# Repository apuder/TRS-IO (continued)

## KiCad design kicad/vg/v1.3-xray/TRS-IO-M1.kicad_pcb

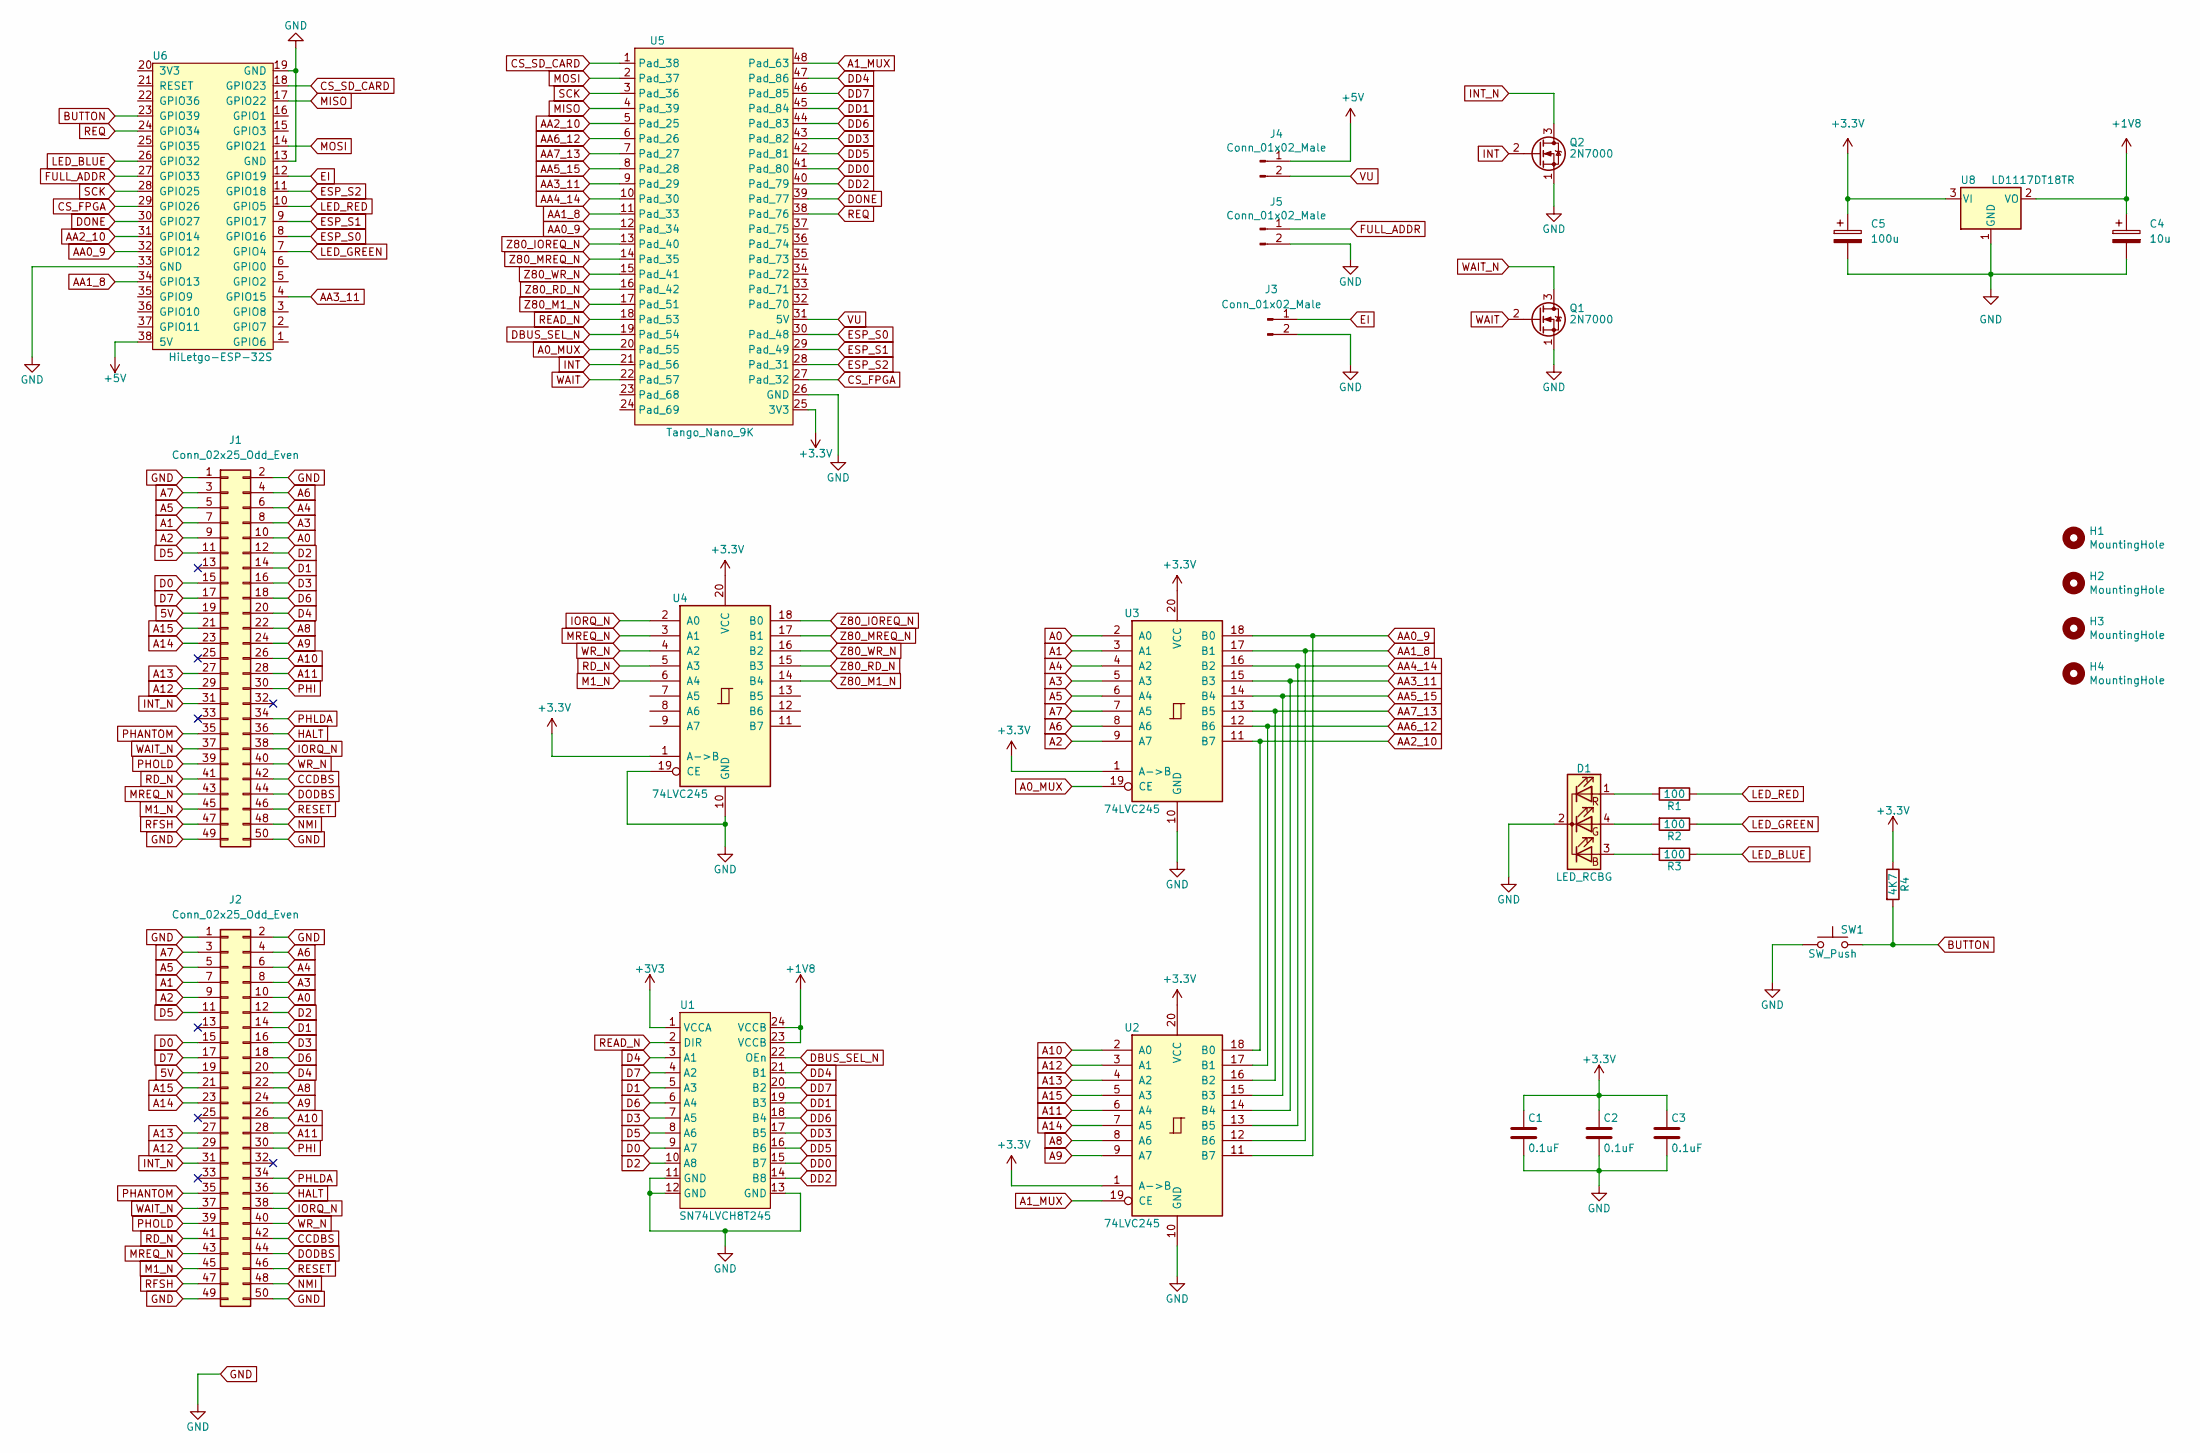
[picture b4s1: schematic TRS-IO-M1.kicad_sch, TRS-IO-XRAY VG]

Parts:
C1, C2, C3: 0.1uF; C_0805_2012Metric_Pad1.18x1.45mm_HandSolder
C4: 10u; C_1206_3216Metric_Pad1.33x1.80mm_HandSolder
C5: 100u; C_1206_3216Metric_Pad1.33x1.80mm_HandSolder
D1: LED_RCBG; LED_D5.0mm-4_RGB
H1, H2, H3, H4: MountingHole; MountingHole_3mm_Pad_Via
J1: Conn_02x25_Odd_Even; EDGE50
J2: Conn_02x25_Odd_Even; Pin_Header_Straight_2x25_Pitch2.54mm
J3, J4, J5: Conn_01x02_Male; PinHeader_1x02_P2.54mm_Vertical
Q1, Q2: 2N7000; TO-92_Inline
R1, R2, R3: 100; R_Axial_DIN0207_L6.3mm_D2.5mm_P7.62mm_Horizontal
R4: 4K7; R_Axial_DIN0207_L6.3mm_D2.5mm_P7.62mm_Horizontal
SW1: SW_Push; SW_PUSH_6mm_H9.5mm
U1: SN74LVCH8T245; TSSOP-24_4.4x7.8mm_P0.65mm
U2, U3, U4: 74LVC245; SSOP-20_5.3x7.2mm_P0.65mm
U5: Tango_Nano_9K; DIP-48_W22.9mm
U6: HiLetgo-ESP-32S; DIP-38_W22.9mm
U8: LD1117DT18TR; TO-252-3_TabPin2

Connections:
5V: J1.19, J2.19
+1V8: C4.1, U1.23 (VCCB), U1.24 (VCCB), U8.2 (VO)
+5V: J4.1, U6.38 (5V)
A0: J1.10, J2.10, U3.2 (A0)
A0_MUX: U3.19 (CE), U5.20 (Pad_55)
A1: J1.7, J2.7, U3.3 (A1)
A1_MUX: U2.19 (CE), U5.48 (Pad_63)
A2: J1.9, J2.9, U3.9 (A7)
A3: J1.8, J2.8, U3.5 (A3)
A4: J1.6, J2.6, U3.4 (A2)
A5: J1.5, J2.5, U3.6 (A4)
A6: J1.4, J2.4, U3.8 (A6)
A7: J1.3, J2.3, U3.7 (A5)
A8: J1.22, J2.22, U2.8 (A6)
A9: J1.24, J2.24, U2.9 (A7)
A10: J1.26, J2.26, U2.2 (A0)
A11: J1.28, J2.28, U2.6 (A4)
A12: J1.29, J2.29, U2.3 (A1)
A13: J1.27, J2.27, U2.4 (A2)
A14: J1.23, J2.23, U2.7 (A5)
A15: J1.21, J2.21, U2.5 (A3)
AA0_9: U2.11 (B7), U3.18 (B0), U5.12 (Pad_34), U6.32 (GPIO12)
AA1_8: U2.12 (B6), U3.17 (B1), U5.11 (Pad_33), U6.34 (GPIO13)
AA2_10: U2.18 (B0), U3.11 (B7), U5.5 (Pad_25), U6.31 (GPIO14)
AA3_11: U2.14 (B4), U3.15 (B3), U5.9 (Pad_29), U6.4 (GPIO15)
AA4_14: U2.13 (B5), U3.16 (B2), U5.10 (Pad_30)
AA5_15: U2.15 (B3), U3.14 (B4), U5.8 (Pad_28)
AA6_12: U2.17 (B1), U3.12 (B6), U5.6 (Pad_26)
AA7_13: U2.16 (B2), U3.13 (B5), U5.7 (Pad_27)
BUTTON: R4.2, SW1.2, U6.23 (GPIO39)
CCDBS: J1.42, J2.42
CS_FPGA: U5.27 (Pad_32), U6.29 (GPIO26)
CS_SD_CARD: U5.1 (Pad_38), U6.18 (GPIO23)
D0: J1.15, J2.15, U1.9 (A7)
D1: J1.14, J2.14, U1.5 (A3)
D2: J1.12, J2.12, U1.10 (A8)
D3: J1.16, J2.16, U1.7 (A5)
D4: J1.20, J2.20, U1.3 (A1)
D5: J1.11, J2.11, U1.8 (A6)
D6: J1.18, J2.18, U1.6 (A4)
D7: J1.17, J2.17, U1.4 (A2)
DBUS_SEL_N: U1.22 (OEn), U5.19 (Pad_54)
DD0: U1.15 (B7), U5.41 (Pad_80)
DD1: U1.19 (B3), U5.45 (Pad_84)
DD2: U1.14 (B8), U5.40 (Pad_79)
DD3: U1.17 (B5), U5.43 (Pad_82)
DD4: U1.21 (B1), U5.47 (Pad_86)
DD5: U1.16 (B6), U5.42 (Pad_81)
DD6: U1.18 (B4), U5.44 (Pad_83)
DD7: U1.20 (B2), U5.46 (Pad_85)
DODBS: J1.44, J2.44
DONE: U5.39 (Pad_77), U6.30 (GPIO27)
EI: J3.1, U6.12 (GPIO19)
ESP_S0: U5.30 (Pad_48), U6.8 (GPIO16)
ESP_S1: U5.29 (Pad_49), U6.9 (GPIO17)
ESP_S2: U5.28 (Pad_31), U6.11 (GPIO18)
FULL_ADDR: J5.1, U6.27 (GPIO33)
GND: C1.2, C2.2, C3.2, C4.2, C5.2, D1.2 (K), J1.1, J1.2, J1.49, J1.50, J2.1, J2.2, J2.49, J2.50, J3.2, J5.2, Q1.1 (S), Q2.1 (S), SW1.1, U1.11 (GND), U1.12 (GND), U1.13 (GND), U2.10 (GND), U3.10 (GND), U4.10 (GND), U4.19 (CE), U5.26 (GND), U6.13 (GND), U6.19 (GND), U6.33 (GND), U8.1 (GND)
HALT: J1.36, J2.36
INT: Q2.2 (G), U5.21 (Pad_56)
INT_N: J1.31, J2.31, Q2.3 (D)
IORQ_N: J1.38, J2.38, U4.2 (A0)
LED_BLUE: R3.1, U6.26 (GPIO32)
LED_GREEN: R2.1, U6.7 (GPIO4)
LED_RED: R1.1, U6.10 (GPIO5)
M1_N: J1.45, J2.45, U4.6 (A4)
MISO: U5.4 (Pad_39), U6.17 (GPIO22)
MOSI: U5.2 (Pad_37), U6.14 (GPIO21)
MREQ_N: J1.43, J2.43, U4.3 (A1)
NMI: J1.48, J2.48
unnamed: D1.1 (RA), R1.2
unnamed: D1.3 (BA), R3.2
unnamed: D1.4 (GA), R2.2
PHANTOM: J1.35, J2.35
PHI: J1.30, J2.30
PHLDA: J1.34, J2.34
PHOLD: J1.39, J2.39
RD_N: J1.41, J2.41, U4.5 (A3)
READ_N: U1.2 (DIR), U5.18 (Pad_53)
REQ: U5.38 (Pad_76), U6.24 (GPIO34)
RESET: J1.46, J2.46
RFSH: J1.47, J2.47
SCK: U5.3 (Pad_36), U6.28 (GPIO25)
VU: J4.2, U5.31 (5V)
WAIT: Q1.2 (G), U5.22 (Pad_57)
WAIT_N: J1.37, J2.37, Q1.3 (D)
WR_N: J1.40, J2.40, U4.4 (A2)
Z80_IOREQ_N: U4.18 (B0), U5.13 (Pad_40)
Z80_M1_N: U4.14 (B4), U5.17 (Pad_51)
Z80_MREQ_N: U4.17 (B1), U5.14 (Pad_35)
Z80_RD_N: U4.15 (B3), U5.16 (Pad_42)
Z80_WR_N: U4.16 (B2), U5.15 (Pad_41)

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
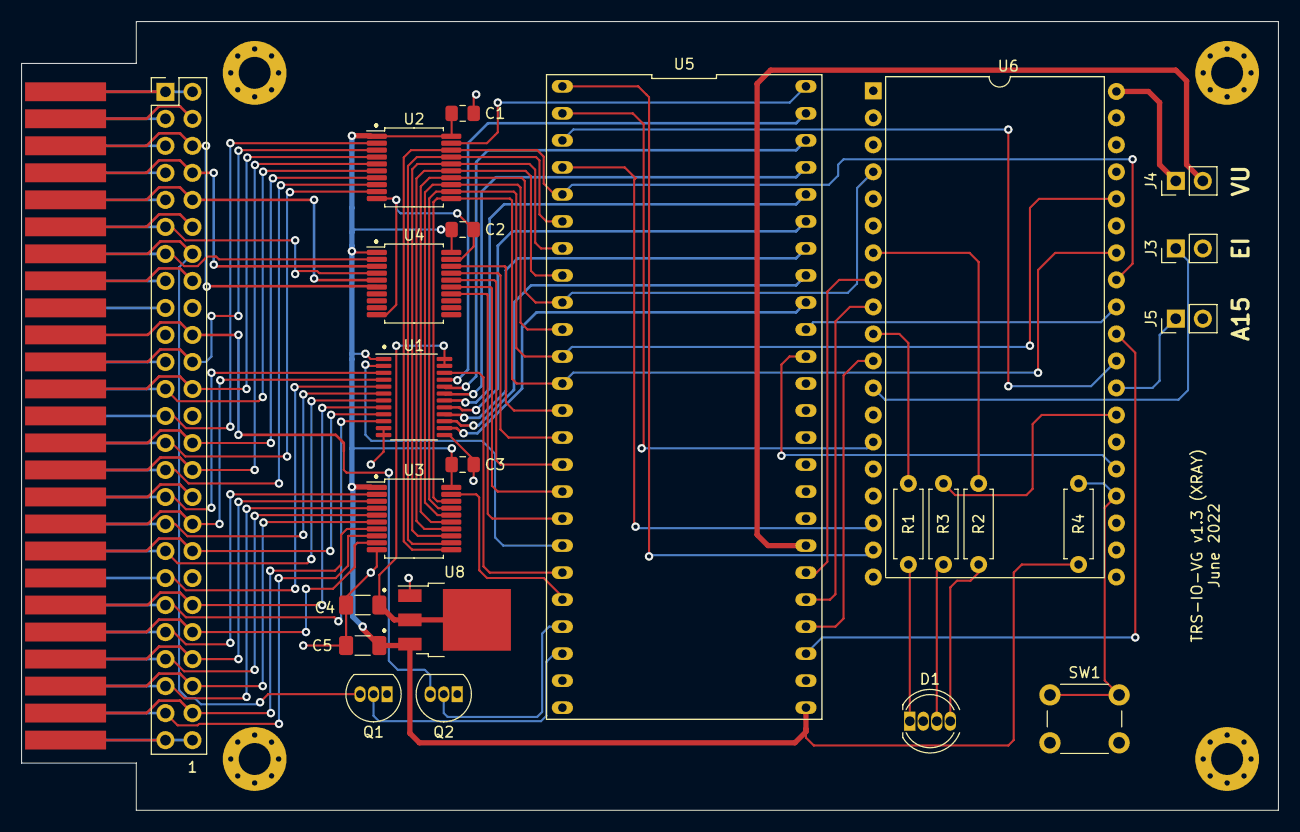
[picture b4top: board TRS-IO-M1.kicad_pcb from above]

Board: 2 copper layers, 118.2 x 74.2 mm, 29 parts (0 on the bottom side), 93 nets.
